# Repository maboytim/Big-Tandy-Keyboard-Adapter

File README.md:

# Big-Tandy-Keyboard-Adapter
PS2 keyboard adapter for 'Big Tandy' computers - Models II, 12, 16, 16B, and 6000.

The keyboard allows you to use a PS2 keyboard with your 'Big Tandy' computer.  There are three versions:

### "A" Version
The A version is for the Models II and 16.  These models have the keyboard cable attached to the computer.  The adapter connects to the end of the cable and the PS2 keyboard to the adapter.

### "B" Version

The B version is for the Models 12, 16B, and 6000.  These models have the keyboard cable attached to the computer.  The adapter plugs directly into the keyboard plug on the front of the computer and the PS2 keyboard into the adapter.

### "AB" Version (universal)
The AB version is for all models.  It has a 5-pin header to connect a pigtail cable.  A pigtail with a male DIN5 connector for Models 12/16B/6000 or a pigtail with a female DIN5 connector for Models II/16.  The pinout differences are also accounted for in the pigtail cable.

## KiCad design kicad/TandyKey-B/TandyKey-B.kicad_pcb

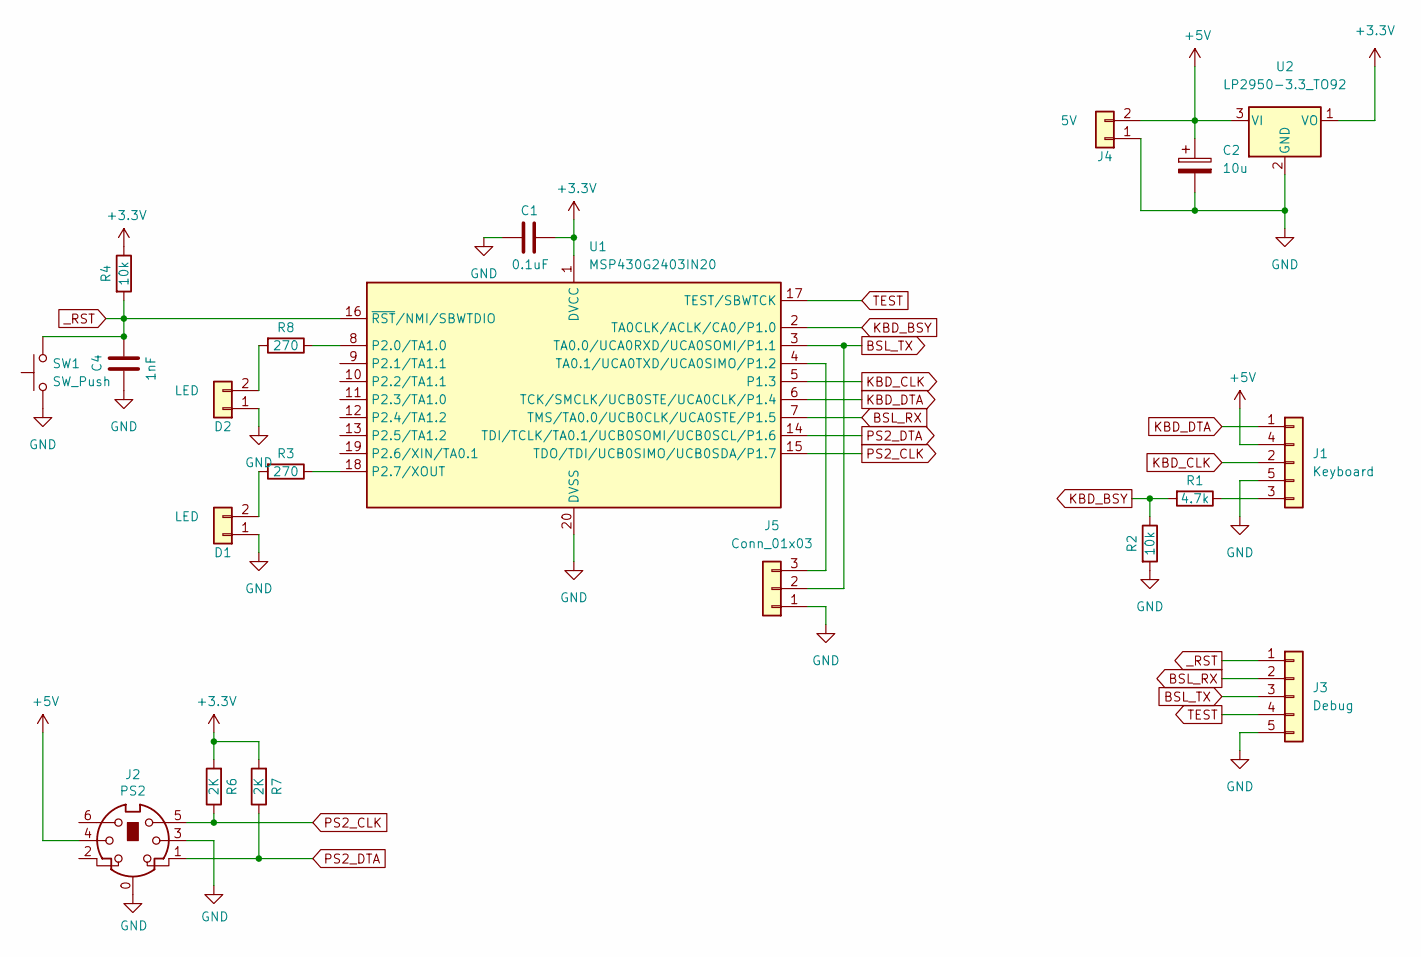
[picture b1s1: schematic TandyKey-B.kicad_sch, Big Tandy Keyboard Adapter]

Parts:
C1: 0.1uF; C_0805_2012Metric_Pad1.18x1.45mm_HandSolder
C2: 10u; C_1206_3216Metric_Pad1.33x1.80mm_HandSolder
C4: 1nF; C_0805_2012Metric_Pad1.18x1.45mm_HandSolder
D1, D2: LED; PinHeader_1x02_P2.54mm_Vertical
J1: Keyboard; DIN5
J2: PS2; minidin_6_ps2_pcb_mount
J3: Debug; PinHeader_1x05_P2.54mm_Vertical
J4: 5V; PinHeader_1x02_P2.54mm_Vertical
J5: Conn_01x03; PinHeader_1x03_P2.54mm_Vertical
R1: 4.7k; R_0805_2012Metric_Pad1.20x1.40mm_HandSolder
R2, R4: 10k; R_0805_2012Metric_Pad1.20x1.40mm_HandSolder
R3, R8: 270; R_0805_2012Metric_Pad1.20x1.40mm_HandSolder
R6, R7: 2K; R_0805_2012Metric_Pad1.20x1.40mm_HandSolder
SW1: SW_Push; PinHeader_1x02_P2.54mm_Vertical
U1: MSP430G2403IN20; DIP-20_W7.62mm
U2: LP2950-3.3_TO92; TO-92_Inline

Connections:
+3V3: C1.1, R4.1, R6.2, R7.2, U1.1 (DVCC), U2.1 (VO)
+5V: C2.1, J1.4, J2.4, J4.2, U2.3 (VI)
BSL_RX: J3.2, U1.7 (TMS/TA0.0/UCB0CLK/UCA0STE/P1.5)
BSL_TX: J3.3, J5.2, U1.3 (TA0.0/UCA0RXD/UCA0SOMI/P1.1)
GND: C1.2, C2.2, C4.2, D1.1, D2.1, J1.5, J2.0, J2.3, J3.5, J4.1, J5.1, R2.2, SW1.1, U1.20 (DVSS), U2.2 (GND)
KBD_BSY: R1.2, R2.1, U1.2 (TA0CLK/ACLK/CA0/P1.0)
KBD_CLK: J1.2, U1.5 (P1.3)
KBD_DTA: J1.1, U1.6 (TCK/SMCLK/UCB0STE/UCA0CLK/P1.4)
unnamed: D1.2, R3.2
unnamed: D2.2, R8.2
unnamed: J1.3, R1.1
unnamed: J5.3, U1.4 (TA0.1/UCA0TXD/UCA0SIMO/P1.2)
unnamed: R3.1, U1.18 (P2.7/XOUT)
unnamed: R8.1, U1.8 (P2.0/TA1.0)
PS2_CLK: J2.5, R6.1, U1.15 (TDO/TDI/UCB0SIMO/UCB0SDA/P1.7)
PS2_DTA: J2.1, R7.1, U1.14 (TDI/TCLK/TA0.1/UCB0SOMI/UCB0SCL/P1.6)
TEST: J3.4, U1.17 (TEST/SBWTCK)
_RST: C4.1, J3.1, R4.2, SW1.2, U1.16 (~RST/NMI/SBWTDIO)

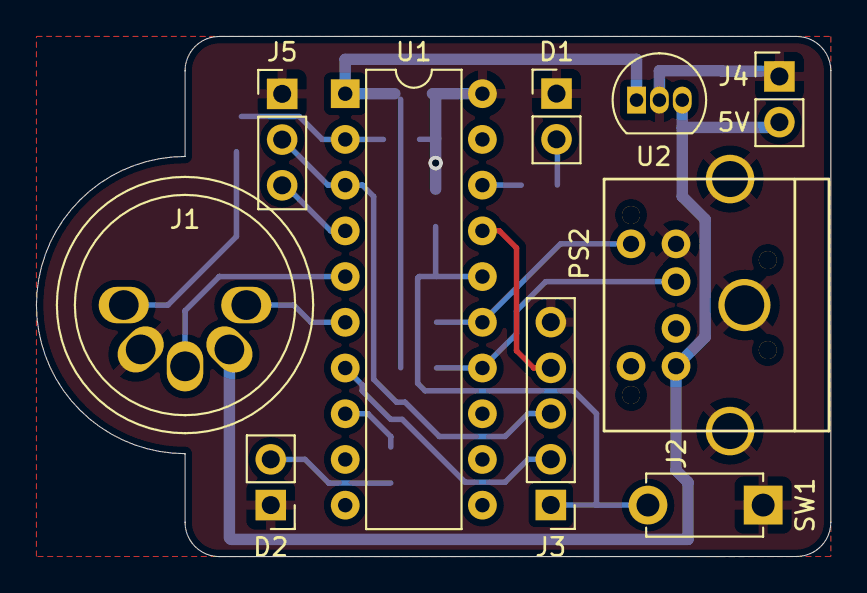
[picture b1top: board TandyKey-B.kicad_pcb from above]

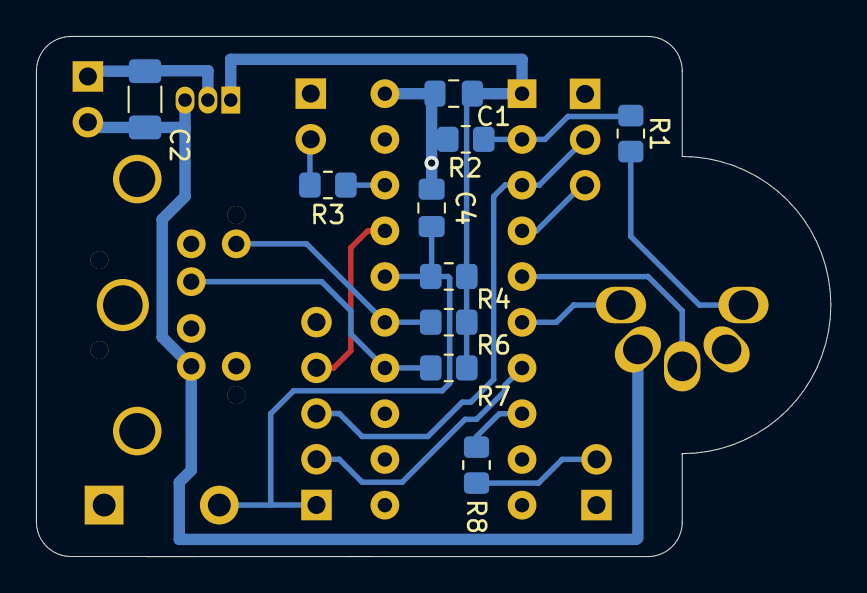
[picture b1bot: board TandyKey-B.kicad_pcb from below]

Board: 2 copper layers, 44.1 x 28.9 mm, 20 parts (10 on the bottom side), 18 nets.

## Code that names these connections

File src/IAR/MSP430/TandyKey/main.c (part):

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// P1
// Tandy keyboard (output)
#define KBD_BSYN BIT0  // input
#define KBD_CLK  BIT3  // output
#define KBD_DTA  BIT4  // output

// PS2 keyboard (input)
#define PS2_DTA  BIT6  // input
#define PS2_CLK  BIT7  // input

// UART (input/output)
#define UART_RX  BIT1  // input (also BSL_TX)
#define UART_TX  BIT2  // output

// BSL
// used by bootstrap loader
#define BSL_TX   BIT1
#define BSL_RX   BIT5

// P2
// LED's
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   // Enable global interrupts
   __enable_interrupt();

   uint8_t ps2_dta = 0, prev_ps2_dta = 0, prev_prev_ps2_dta = 0;
   uint8_t ps2_shft = 0, ps2_ctrl = 0, ps2_alt = 0;
   while(1)
      {
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
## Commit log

2022-11-01 Initial commit of all files to the repository
